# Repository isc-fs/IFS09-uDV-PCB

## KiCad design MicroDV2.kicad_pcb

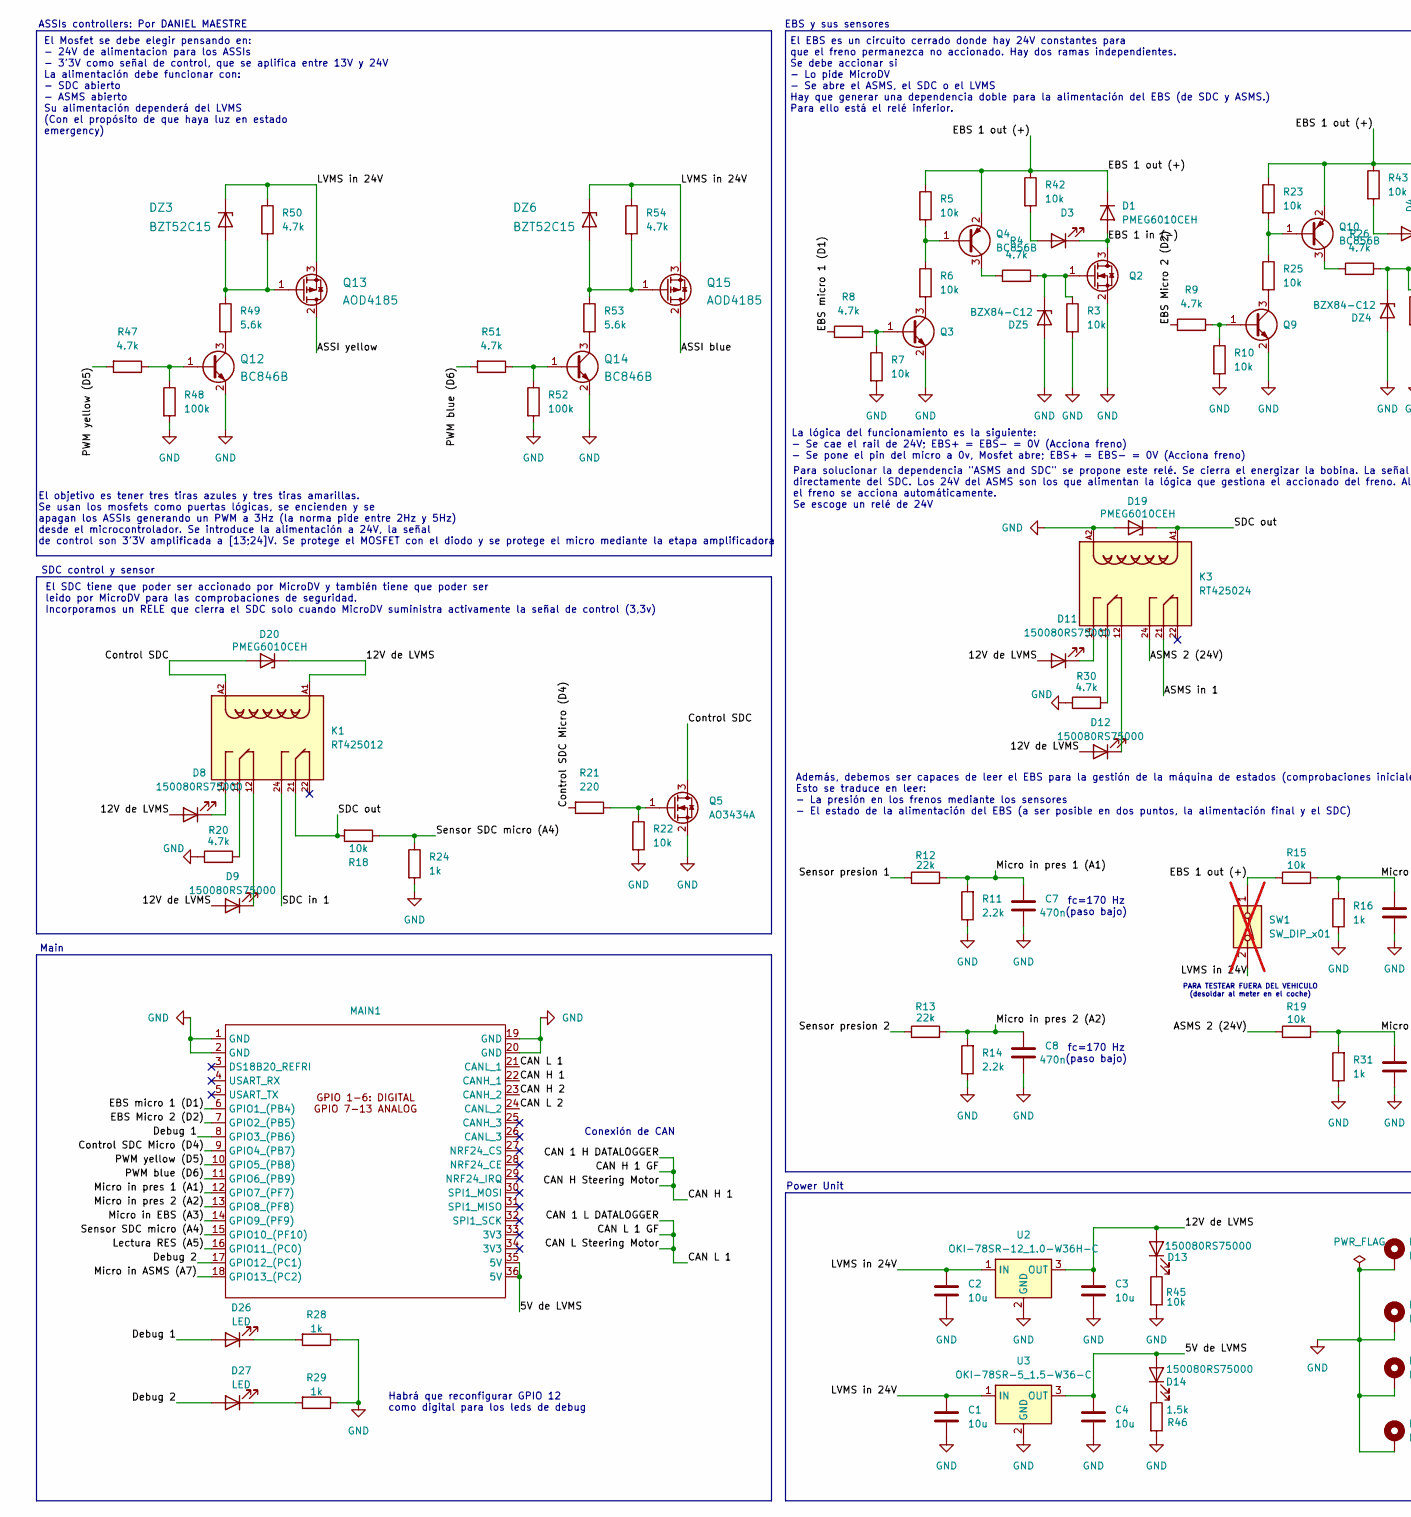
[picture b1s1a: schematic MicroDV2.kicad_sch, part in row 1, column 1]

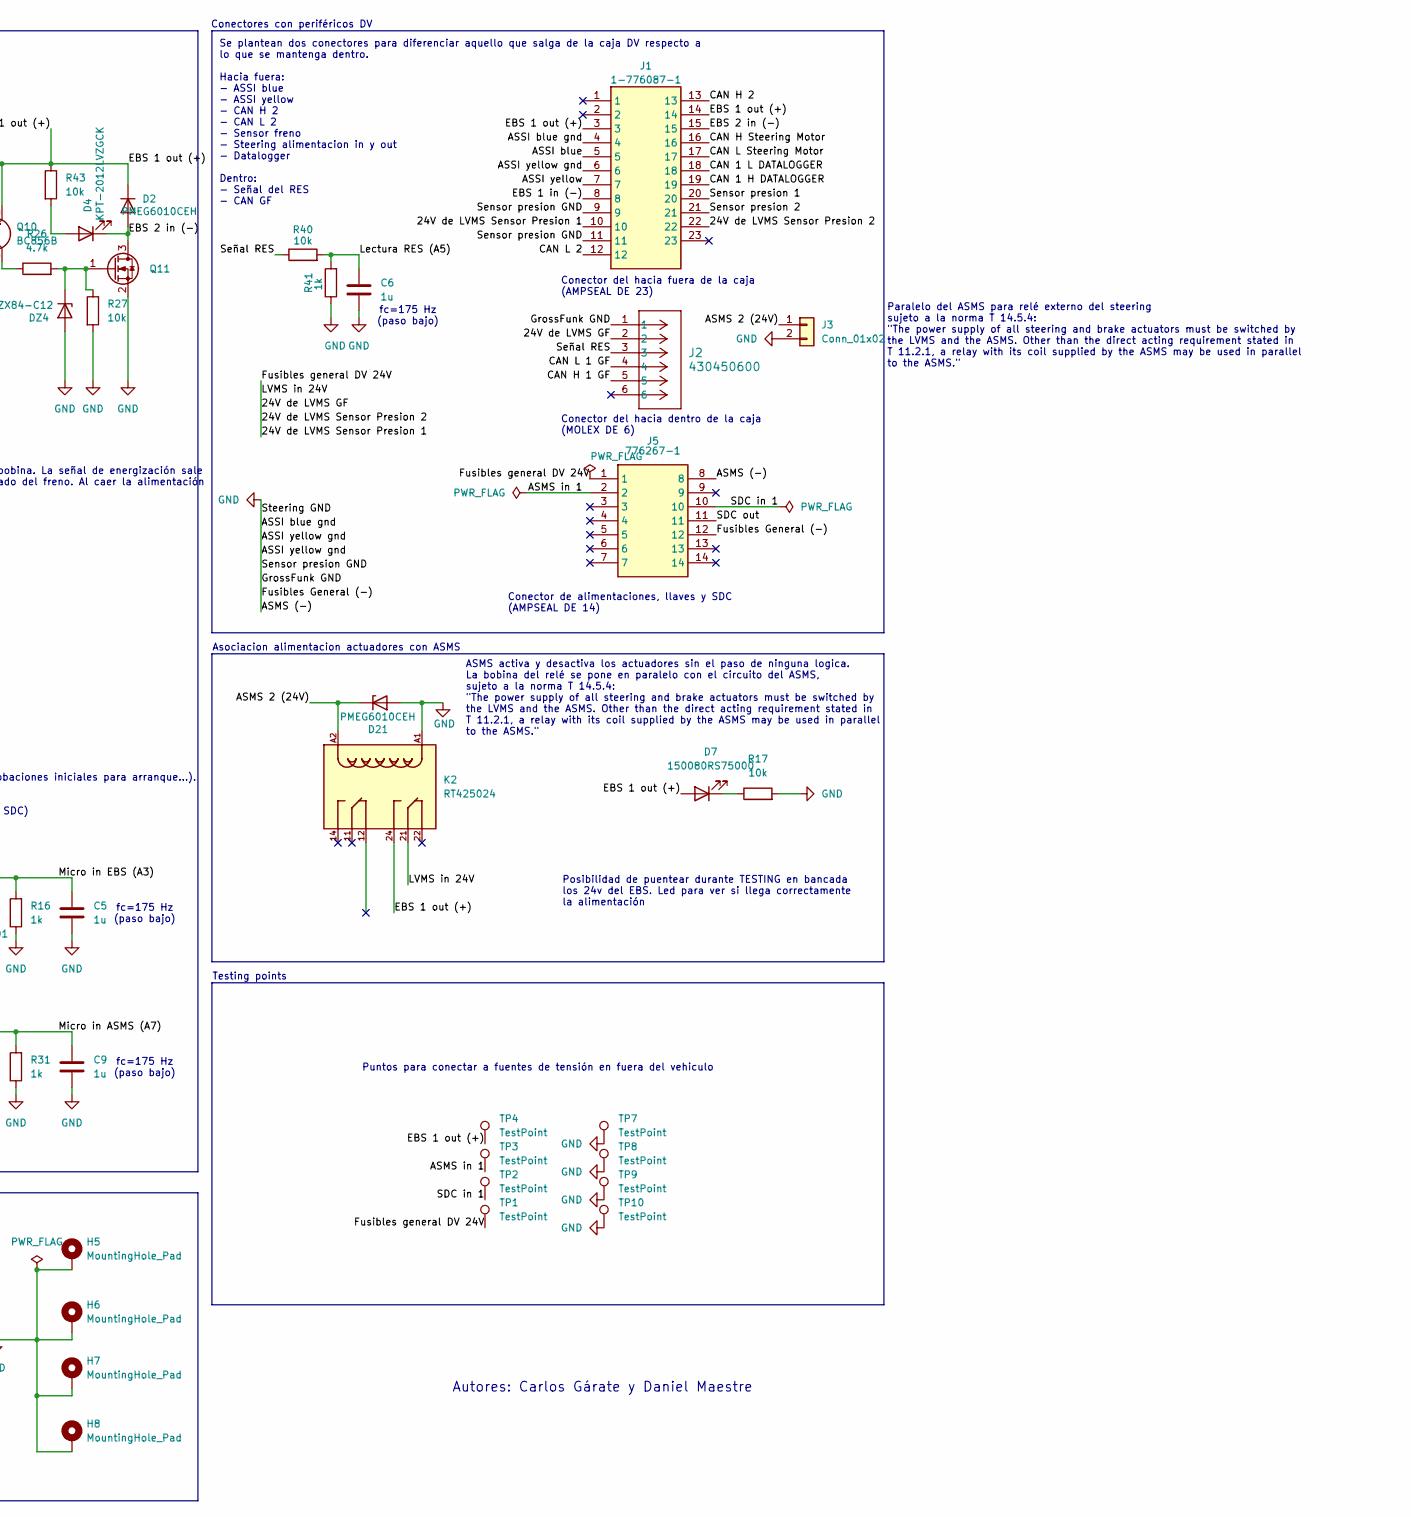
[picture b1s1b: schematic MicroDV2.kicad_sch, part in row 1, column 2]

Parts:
C1, C2, C3, C4: 10u; C_0805_2012Metric
C5, C6, C9: 1u; C_0805_2012Metric
C7, C8: 470n; C_0805_2012Metric
D1, D2, D19, D20, D21: PMEG6010CEH; D_SOD-123F
D3, D4: KPT-2012LVZGCK; LED_0805_2012Metric
D7, D8, D9, D11, D12, D13, D14: 150080RS75000; 150080RS75000_WRE
D26, D27: LED; 150080RS75000_WRE
DZ3, DZ6: BZT52C15; D_SOD-123
DZ4, DZ5: BZX84-C12; SOT-23
H5, H7, H8: MountingHole_Pad; MountingHole_3.2mm_M3_DIN965_Pad
H6: MountingHole_Pad; MountingHole_3.2mm_Pad5.3
J1: 1-776087-1; AMPSEAL_23_edge_silk; Mouser Part Number 571-1-776087-1
J2: 430450600; MicroFit_6_edge_silk
J3: Conn_01x02; MicroFit_2_edge_silk; Part Number 1-0201FBV0T
J5: 776267-1; AMPSEAL_14_edge_silk; Manufacturer_Part_Number 776267-1
K1: RT425012; Relay_DPDT_Schrack-RT2-FormC_RM5mm; PARTREV 04-11
K2, K3: RT425024; Relay_DPDT_Schrack-RT2-FormC_RM5mm
MAIN1: MAIN_LITE
Q2, Q11: PMV37ENEA; SOT-23
Q3, Q9, Q12, Q14: BC846B; SOT-23
Q4, Q10: BC856B; SOT-23
Q5: AO3434A; SOT-23
Q13, Q15: AOD4185; TO-252-2
R3, R5, R6, R7, R10, R15, R17, R18, R19, R22, R23, R25, R27, R40, R42, R43, R45: 10k; 0805_PAN
R4, R8, R9, R20, R26, R30, R47, R50, R51, R54: 4.7k; 0805_PAN
R11, R14: 2.2k; 0805_PAN
R12, R13: 22k; 0805_PAN
R16, R24, R28, R29, R31, R41: 1k; 0805_PAN
R21: 220; 0805_PAN
R46: 1.5k; 0805_PAN
R48, R52: 100k; 0805_PAN
R49, R53: 5.6k; 0805_PAN
SW1: SW_DIP_x01; SW_DIP_SPSTx01_Slide_9.78x4.72mm_W7.62mm_P2.54mm; not fitted
TP1, TP2, TP3, TP4, TP7, TP8, TP9, TP10: TestPoint; TestPoint_Keystone_5000-5004_Miniature
U2: OKI-78SR-12_1.0-W36H-C; Converter_DCDC_Murata_OKI-78SR_Horizontal
U3: OKI-78SR-5_1.5-W36-C; Converter_DCDC_Murata_OKI-78SR_Vertical

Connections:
/5V de LVMS: C4.1, D14.2 (A), MAIN1.35 (5V), MAIN1.36 (5V), U3.3 (OUT)
/12V de LVMS: C3.1, D8.2 (A), D9.2 (A), D11.2 (A), D12.2 (A), D13.2 (A), D20.1 (K), K1.A1, U2.3 (OUT)
/24V de LVMS GF: C1.1, C2.1, DZ3.1 (K), DZ6.1 (K), J1.10, J1.22, J2.2, J5.1, K2.21, Q13.3 (S), Q15.3 (S), R50.1, R54.1, SW1.2, TP1.1 (1_1), U2.1 (IN), U3.1 (IN)
/ASMS 2 (24V): D21.1 (K), J3.1, K2.A2, K3.24, R19.1
/ASMS in 1: J5.2, K3.21, TP3.1 (1_1)
/ASSI blue: J1.5, Q15.2 (D)
/ASSI yellow: J1.7, Q13.2 (D)
/CAN 1 H DATALOGGER: J1.16, J1.19, J2.5, MAIN1.22 (CANH_1)
/CAN 1 L DATALOGGER: J1.17, J1.18, J2.4, MAIN1.21 (CANL_1)
/CAN H 2: J1.13, MAIN1.23 (CANH_2)
/CAN L 2: J1.12, MAIN1.24 (CANL_2)
/Control SDC: D20.2 (A), K1.A2, Q5.3 (D)
/Control SDC Micro (D4): MAIN1.9 (GPIO4_(PB7)), R21.2
/Debug 1: D26.2 (A), MAIN1.8 (GPIO3_(PB6))
/Debug 2: D27.2 (A), MAIN1.17 (GPIO12_(PC1))
/EBS 1 in (-): D1.2 (A), D3.1 (K), J1.8, Q2.3 (D)
/EBS 1 out (+): D1.1 (K), D2.1 (K), D7.2 (A), J1.3, J1.14, K2.24, Q4.2 (E), Q10.2 (E), R5.1, R15.1, R23.1, R42.1, R43.1, SW1.1, TP4.1 (1_1)
/EBS 2 in (-): D2.2 (A), D4.1 (K), J1.15, Q11.3 (D)
/EBS Micro 2 (D2): MAIN1.7 (GPIO2_(PB5)), R9.1
/EBS micro 1 (D1): MAIN1.6 (GPIO1_(PB4)), R8.1
/Lectura RES (A5): C6.1, MAIN1.16 (GPIO11_(PC0)), R40.2, R41.2
/Micro in ASMS (A7): C9.1, MAIN1.18 (GPIO13_(PC2)), R19.2, R31.2
/Micro in EBS (A3): C5.1, MAIN1.14 (GPIO9_(PF9)), R15.2, R16.2
/Micro in pres 1 (A1): C7.1, MAIN1.12 (GPIO7_(PF7)), R11.2, R12.2
/Micro in pres 2 (A2): C8.1, MAIN1.13 (GPIO8_(PF8)), R13.2, R14.2
/PWM blue (D6): MAIN1.11 (GPIO6_(PB9)), R51.2
/PWM yellow (D5): MAIN1.10 (GPIO5_(PB8)), R47.2
/SDC in 1: J5.10, K1.24, TP2.1 (1_1)
/SDC out: D19.1 (K), J5.11, K1.21, K3.A1, R18.2
/Sensor SDC micro (A4): MAIN1.15 (GPIO10_(PF10)), R18.1, R24.1
/Sensor presion 1: J1.20, R12.1
/Sensor presion 2: J1.21, R13.1
/Señal RES: J2.3, R40.1
GND: C1.2, C2.2, C3.2, C4.2, C5.2, C6.2, C7.2, C8.2, C9.2, D19.2 (A), D21.2 (A), DZ4.1 (A), DZ5.1 (A), H5.1 (1_1), H6.1 (1_1), H7.1 (1_1), H8.1 (1_1), J1.4, J1.6, J1.9, J1.11, J2.1, J3.2, J5.8, J5.12, K2.A1, K3.A2, MAIN1.1 (GND), MAIN1.2 (GND), MAIN1.19 (GND), MAIN1.20 (GND), Q2.2 (S), Q3.2 (E), Q5.2 (S), Q9.2 (E), Q11.2 (S), Q12.2 (E), Q14.2 (E), R3.2, R7.2, R10.2, R11.1, R14.1, R16.1, R17.2, R20.1, R22.2, R24.2, R27.2, R28.1, R29.1, R30.1, R31.1, R41.1, R45.2, R46.2, R48.2, R52.2, TP7.1 (1_1), TP8.1 (1_1), TP9.1 (1_1), TP10.1 (1_1), U2.2 (GND), U3.2 (GND)
unnamed: D3.2 (A), R42.2
unnamed: D4.2 (A), R43.2
unnamed: D7.1 (K), R17.1
unnamed: D8.1 (K), K1.14
unnamed: D9.1 (K), K1.12
unnamed: D11.1 (K), K3.14
unnamed: D12.1 (K), K3.12
unnamed: D13.1 (K), R45.1
unnamed: D14.1 (K), R46.1
unnamed: D26.1 (K), R28.2
unnamed: D27.1 (K), R29.2
unnamed: DZ3.2 (A), Q13.1 (G), R49.1, R50.2
unnamed: DZ4.3 (K), Q11.1 (G), R26.2, R27.1
unnamed: DZ5.3 (K), Q2.1 (G), R3.1, R4.2
unnamed: DZ6.2 (A), Q15.1 (G), R53.1, R54.2
unnamed: K1.11, R20.2
unnamed: K3.11, R30.2
unnamed: Q3.1 (B), R7.1, R8.2
unnamed: Q3.3 (C), R6.2
unnamed: Q4.1 (B), R5.2, R6.1
unnamed: Q4.3 (C), R4.1
unnamed: Q5.1 (G), R21.1, R22.1
unnamed: Q9.1 (B), R9.2, R10.1
unnamed: Q9.3 (C), R25.2
unnamed: Q10.1 (B), R23.2, R25.1
unnamed: Q10.3 (C), R26.1
unnamed: Q12.1 (B), R47.1, R48.1
unnamed: Q12.3 (C), R49.2
unnamed: Q14.1 (B), R51.1, R52.1
unnamed: Q14.3 (C), R53.2

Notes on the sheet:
fc=175 Hz (paso bajo)
fc=170 Hz (paso bajo)
Puntos para conectar a fuentes de tensión en fuera del vehiculo
Además, debemos ser capaces de leer el EBS para la gestión de la máquina de estados (comprobaciones iniciales para arranque...). Esto se traduce en leer: - La presión en los frenos mediante los sensores - El estado de la alimentación del EBS (a ser posible en dos puntos, la alimentación final y el 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
Paralelo del ASMS para relé externo del steering sujeto a la norma T 14.5.4: "The power supply of all steering and brake actuators must be switched by the LVMS and the ASMS. Other than the direct acting requirement stated in T 11.2.1, a relay with its coil supplied by the ASMS may be used in parall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
Para solucionar la dependencia "ASMS and SDC" se propone este relé. Se cierra el energizar la bobina. La señal de energización sale directamente del SDC. Los 24V del ASMS son los que alimentan la lógica que gestiona el accionado del freno. Al caer la alimentación el freno se acciona automáticamente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
Conector del hacia fuera de la caja (AMPSEAL DE 23)
Conector del hacia dentro de la caja (MOLEX DE 6)
Main
Conector de alimentaciones, llaves y SDC (AMPSEAL DE 14)
Habrá que reconfigurar GPIO 12 como digital para los leds de debug
Power Unit
Autores: Carlos Gárate y Daniel Maestre
Posibilidad de puentear durante TESTING en bancada los 24v del EBS. Led para ver si llega correctamente la alimentación
El SDC tiene que poder ser accionado por MicroDV y también tiene que poder ser leido por MicroDV para las comprobaciones de seguridad. Incorporamos un RELE que cierra el SDC solo cuando MicroDV suministra activamente la señal de control (3,3v)
Conexión de CAN
Se plantean dos conectores para diferenciar aquello que salga de la caja DV respecto a lo que se mantenga dentro. Hacia fuera: - ASSI blue - ASSI yellow - CAN H 2 - CAN L 2 - Sensor freno - Steering alimentacion in y out - Datalogger Dentro: - Señal del RES - CAN GF
PARA TESTEAR FUERA DEL VEHICULO (desoldar al meter en el coche)
El EBS es un circuito cerrado donde hay 24V constantes para que el freno permanezca no accionado. Hay dos ramas independientes. Se debe accionar si - Lo pide MicroDV - Se abre el ASMS, el SDC o el LVMS Hay que generar una dependencia doble para la alimentación del EBS (de SDC y ASMS.) Para ello est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
ASMS activa y desactiva los actuadores sin el paso de ninguna logica. La bobina del relé se pone en paralelo con el circuito del ASMS, sujeto a la norma T 14.5.4: "The power supply of all steering and brake actuators must be switched by the LVMS and the ASMS. Other than the direct acting requiremen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
La lógica del funcionamiento es la siguiente: - Se cae el rail de 24V; EBS+ = EBS- = 0V (Acciona freno) - Se pone el pin del micro a 0v, Mosfet abre; EBS+ = EBS- = 0V (Acciona freno)
El Mosfet se debe elegir pensando en: - 24V de alimentacion para los ASSIs - 3'3V como señal de control, que se aplifica entre 13V y 24V La alimentación debe funcionar con: - SDC abierto - ASMS abierto Su alimentación dependerá del LVMS (Con el propósito de que haya luz en estado emergency)
ASSIs controllers: Por DANIEL MAESTRE
SDC control y sensor
Conectores con periféricos DV
El objetivo es tener tres tiras azules y tres tiras amarillas. Se usan los mosfets como puertas lógicas, se encienden y se apagan los ASSIs generando un PWM a 3Hz (la norma pide entre 2Hz y 5Hz) desde el microcontrolador. Se introduce la alimentación a 24V, la señal de control son 3'3V amplificada 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
Asociacion alimentacion actuadores con ASMS
Testing points
EBS y sus sensores

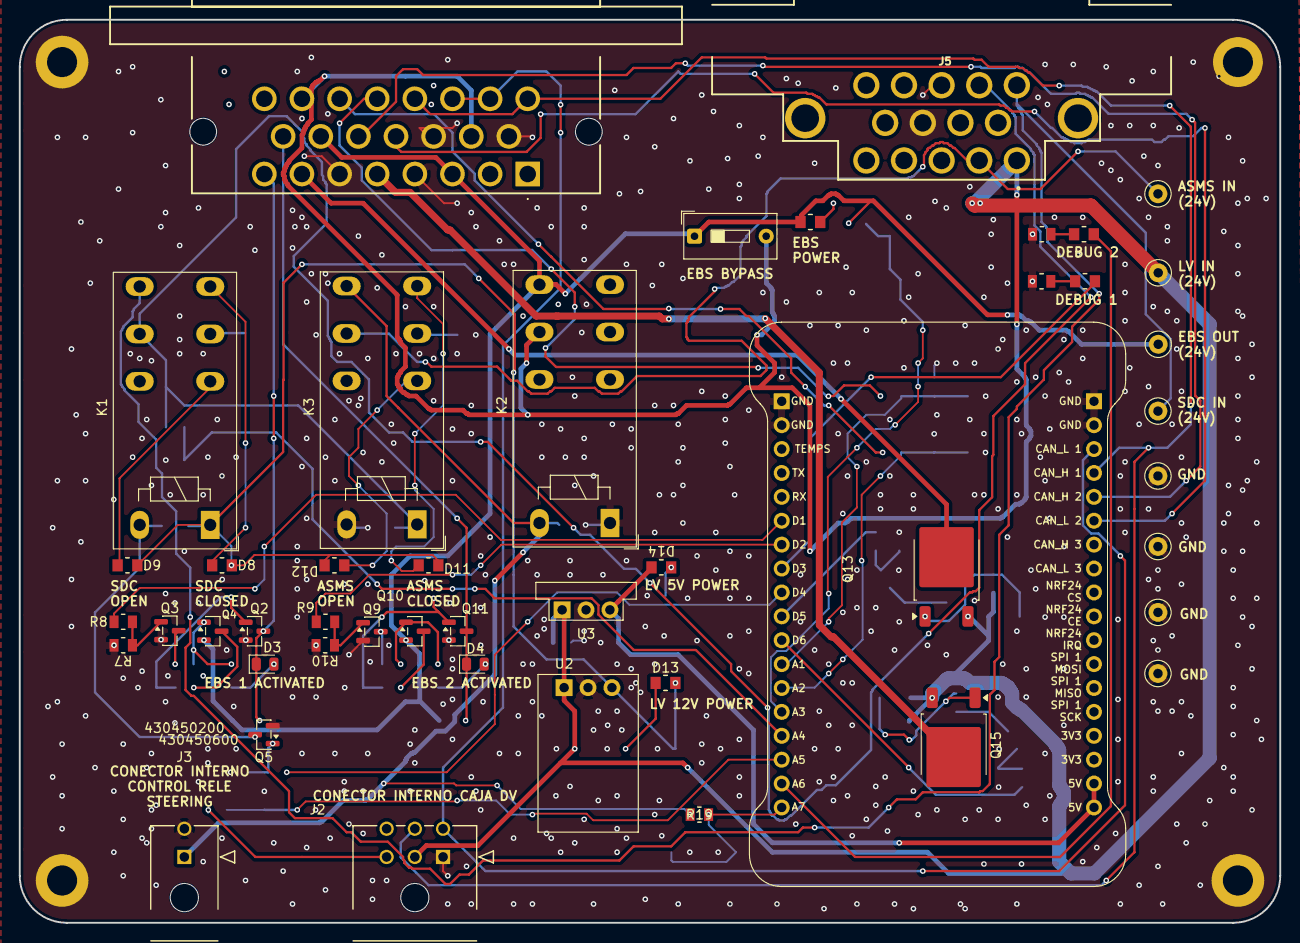
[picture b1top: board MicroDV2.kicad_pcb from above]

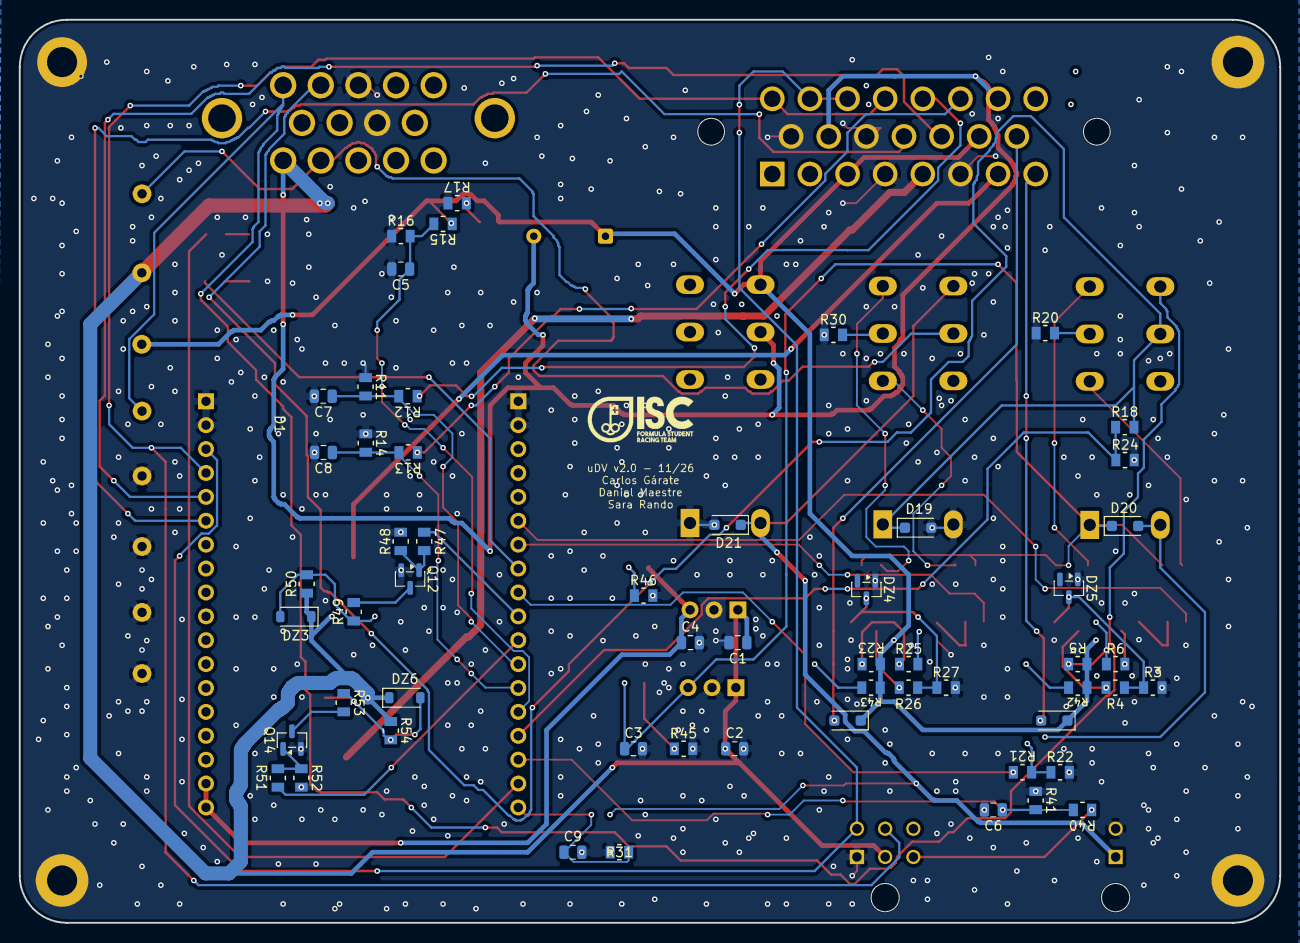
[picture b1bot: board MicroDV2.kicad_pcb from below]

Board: 2 copper layers, 134.0 x 96.0 mm, 107 parts (57 on the bottom side), 64 nets.

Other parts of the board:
G3: LOGO; LogoISC
